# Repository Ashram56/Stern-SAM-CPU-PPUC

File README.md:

# Stern SAM CPU PPUC

A replacement CPU board for the Stern SAM pinball platform. A Raspberry Pi runs the original game ROM under PinMAME
through the [PPUC](https://github.com/PPUC) stack. An RP2354B on the same board drives the original IO power board bus (J1)
with its PIO, reads the switch matrix, dedicated switches and DIP switches, and can scan the original DMD.

- [docs/ARCHITECTURE.md](docs/ARCHITECTURE.md): architecture, bus timing, pin budget, safety, and open questions.
- [docs/reference/](docs/reference/): Stern SAM manual extracts (IO power driver and CPU/Sound board schematics, backbox,
  playfield, cabinet and coin door wiring).

Background:
- [Tron-Legacy-LE-ROM-Decryption/io/bus](https://github.com/Ashram56/Tron-Legacy-LE-ROM-Decryption/tree/main/io/bus):
  the CPU to IO board bus as the SAM ROM drives it.
- [Stern-SAM-Databus-Analysis](https://github.com/Ashram56/Stern-SAM-Databus-Analysis): J1 pinout and IO board schematic notes.

## Licence

- Firmware and software: GNU GPL v3 ([LICENSE](LICENSE)), matching PPUC.
- Hardware design files: CERN Open Hardware Licence v2, strongly reciprocal ([LICENSE-HARDWARE](LICENSE-HARDWARE)).
- The manual extracts in `docs/reference/` are Stern Pinball's material, kept for reference, and are not covered by
  either licence.

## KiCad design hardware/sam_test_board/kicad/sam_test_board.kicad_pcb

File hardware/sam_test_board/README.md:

# SAM universal test board (carte de test universelle, 48 voies)

One small board, made four times (JLCPCB batch of 5: one spare), that replaces the playfield and switch harnesses so
the new CPU board and the I/O Power Driver board 520-5249-00 can be tested with nothing at risk. Chosen by Vincent on
2026-11-18 instead of the single 250 x 150 mm board of `../driver_test_board/` (draft 0.1, abandoned).

## One channel (× 48)

Each pin of the four KK-396 12-pin headers A-D is a universal channel:

- **Load and indicator**: header common COMx → 33 k (0.5 W) → red LED → pin, green LED back in parallel. With COMx on a rail,
  a low-side output that turns on lights red (about 1.4 mA at 50 V, 0.5 mA at 20 V); with COMx on GND, an output
  that drives high lights green. A 3-pad solder jumper per header (JP1-JP4) puts COMx on RAILx (J5), on GND, or
  leaves it open (switch simulation, sense only).
- **Sense**: 100 k / 220 k (header A: 22 k 0.5 W / 47 k) into a 74HC165 input, whose clamp diode holds the node at 3.3 V
  up to 50 V (0.46 mA, header A 2.1 mA). 3 × 220 R load the 3.3 V rail (45 mA) so the clamp current cannot lift it.
  Header A also goes straight to GPIO8-19: fast enough for the 300 ns aux strobes and the CPU switch strobes.
- **Drive**: BSS123 (100 V, 170 mA) from pin to ground, gate from a 74HCT595 chain (100 k pull-down), to close a
  simulated switch.

## Roles

Same board and firmware, role set by the JP9/JP10 solder jumpers. Cables are straight: pin n of the SAM connector on
pin n of the header (a 9 or 10 way housing plugs on pins 1-9 / 1-10).

| role | JP9 / JP10 | A | B | C | D | commons |
|---|---|---|---|---|---|---|
| coils | open / open | IO J8 (1-8) | IO J9 (9-16) | IO J7 (17-24) | IO J6 (25-32) | A, B on +50 V, C, D on +20 V (J5) |
| lamps + aux | closed / open | IO J3 (aux strobes 9-12) | IO J12 (lamp strobes) | IO J13 (lamp columns) | IO J2 (aux data) | per the output type, see below |
| switch matrix | open / closed | CPU J1 (strobes) | CPU J6 (returns 1-8) | CPU J12 (returns 9-16) | CPU J2 (D-1..D-8) | open |
| dedicated | closed / closed | CPU J3 (D-9..D-16) | CPU J13 (D-17..D-24) | free | free | open |

Coil outputs have a 1N4004 flyback diode to their rail on the driver board: the rails must be on (J5 RAILx and the
driver board), otherwise every output reads ON through its diode. For the lamp board, an output that pulls low needs
its header common on the matching rail (red LED), one that drives high needs the common on GND (green LED); +18 V
also arrives on J13 pin 9, so channel C9 reads high (check the J13 9/10 swap on your IO board).

## Files

- `kicad/`: KiCad 9 schematic 0.2 (ERC 0, `kicad/erc.rpt`), PCB `sam_test_board.kicad_pcb` (DRC `kicad/drc.rpt`),
  project footprint library `sam_test_board.pretty` (PS1).
- `sam_test_board_schematic_v0.2.pdf`
- `fab/`: JLCPCB gerbers, BOM and CPL, renders (`tools/make_fab.sh`).
- `firmware/`: RP2354B firmware (Pico SDK 2.2), see its README. `pc/stb_probe.py`: PC tool for one or several boards.
- `tools/`: `place_stb.py` (placement from the netlist), `make_pro.py` (net classes), `finish_stb.py` (Freerouting
  session import, GND / GND_USB pours), `jlc_bom.py`, `jlc_rotcheck.py`, `make_fab.sh`. The schematic generator is
  `../driver_test_board/tools/design_stb.py` (`build_dtb.py design_stb <outdir>`, it shares kigen with the large board).
  From now on edit the KiCad files directly; the generators are the record of how the draft was made.

## PCB (0.2, reviewed 2026-11-18)

- 165 x 133 mm, 2 layers, 1.6 mm, every part on the top side (single-sided JLCPCB assembly). Four M3 holes in the
  corners (H1 = ground lug with pad).
- Headers A, B on the top edge, C, D on the bottom edge, J5 (rails + GND) top right, USB-C bottom right. KK-396
  friction ramps face inward.
- One column per channel facing its pin (red, green LED, 33 k, BSS123, 100 k gate, sense divider); the 74HC165 /
  74HCT595 in a strip across the middle under the channels they serve; RP2354B on the right.
- Net classes: HV (header pins, LED nodes, commons, rails): 0.6 mm clearance (IPC-2221 B2), 0.3 mm tracks.
  Default 0.2 / 0.15 mm (0.4 mm pitch QFN). Power 0.4 mm.
- Isolation: GND_USB (PC side) in the bottom-right corner (x > 129 mm, y > 111 mm), a strip with no copper separates
  it from GND; only U3 (ADuM3160) and PS1 (B0505S) straddle it.
- Fully routed: 0 open connection, ERC 0, DRC 0 error (`kicad/erc.rpt`, `kicad/drc.rpt`; the 2 warnings left are the
  USB-C silkscreen at the board edge). JP1-JP4 pads keep a 0.25 mm local clearance (solder jumper, 50 V max).
- Silkscreen: header names and pin numbers, J5 pin names, COM jumper sides (R = rail, G = GND), test point names, the
  role table (JP9 / JP10) and the LED legend.

## Review of 2026-11-18 (0.1 to 0.2)

Fixed:

1. **USB upstream series resistors.** The ADuM3160 needs a series resistor on each of its four data pins; UD+ / UD-
   went straight to the USB-C connector. Added R219 / R220 (24 R) between the connector (and its USBLC6) and U3.
2. **Power in the 50 V resistors.** Header A sense resistors (22 k) dissipate 96 mW at 50 V and 123 mW at 56 V on a
   125 mW 0805; the 33 k LED resistors 70 to 88 mW. Both are now 0.5 W 0805 parts (Panasonic ERJ-P06: C441987,
   C441956), same footprint: 25 % and 18 % of rating at 56 V.
3. **DC/DC module body.** PS1 used a bare 4-pin header footprint; the B0505S body (11.6 x 6.0 mm) reaches 4.8 mm
   left of the pin row and came within 0.3 mm of the C5 / C8 pads. PS1 now has its real outline and courtyard
   (`kicad/sam_test_board.pretty`), C5 / C8 are turned and moved (1.5 mm from the body).
4. **ADuM3160 decoupling.** C2 (VBUS1) and C3 / C4 (VDD1) were 5 to 9 mm from their pins; they now sit under pins
   1-2 and 3-5, each with its own via to the GND_USB return.
5. **4 open connections routed**: +1V1 to U5 pin 10 (via inside the QFN ring), COMB to JP2, VBUS_USB to U3 pin 1,
   G_B7 (needed G_B6 and S_B8 re-routed around it).
6. Symbols of test points, jumpers and holes marked "not in BOM" like their footprints (24 parity warnings gone).
7. Silkscreen labels added (there was no text on the board).

Checked and left as is:

- RP2354B pinout, core regulator, crystal, USB 27 R, QSPI_SS boot button, 74HC165 clamp current (0.46 mA, header A
  2.1 mA, 42 mA in total into +3V3 against 45 mA of fixed load), 74HCT595 at 5 V driving the BSS123 gates, rail
  dividers (2.7 V at 60 V), ADuM3160 strapping (full speed, pull-up always on), B0505S pin order.
- With the common on a rail and an output OFF, the sense divider still draws through the red LED: 0.14 mA on
  B-D (10 % of the ON current), **0.49 mA on header A (one third of ON)**. Header A LEDs glow when OFF; the PC
  reading is not affected. To avoid it use header A for the 20 V / logic connectors when a choice exists.
- NCP1117 with ceramic output capacitors only (10 u + 35 x 100 n): works in practice but is outside the datasheet
  ESR window. If +3V3 rings on the prototype, add a 10 u tantalum across C10 or use an LDO rated for ceramics in a
  later revision.
- BSS123 drives are only limited by the firmware role: closing a channel that is wired to a stiff source (lamp
  column +18 V) would exceed 170 mA.
- Spacing: SOT-23 / 0805 columns are 1.38 to 1.40 mm apart (3.96 mm pin pitch), the USB-C connector has parts at
  2.8 to 3.8 mm (C1, U2, R220, C4), PS1 body 1.5 mm from C5 / C8 / C2: below the 1.5 mm / 4 mm targets.
- Solder jumpers JP1-JP4 bridge 50 V with a 0.3 mm pad gap: never bridge the three pads (rail to GND short).

## JLCPCB

- 433 parts placed by JLC (432 SMD + PS1 B0505S through-hole), 35 LCSC codes, all in stock on the JLC assembly
  library on 2026-11-18 (lowest: 3.3 uH C167673 1 371, 22 k 0.5 W C441987 2 274, 74HCT595 C282339 6 348,
  ADuM3160 C284149 7 939, 33 k 0.5 W C441956 8 873).
- Hand soldered: the five KK-396 headers (Molex 26-60-4120 x 4, 26-60-4060), SWD and SYNC headers.
- CPL rotations checked against the EasyEDA footprint of each LCSC part (`tools/jlc_rotcheck.py`): offsets in
  `jlc_bom.py` (SOIC and SOT-23-6 +270, BSS123 and NCP1117 +180, B0505S +270 with its origin at the centre, USB-C
  origin shifted 1.575 mm). The tool prints CHECK for the LEDs, the NCP1117 and the buttons because their pad
  numbers differ; compared by pin name / position they are right (LED cathodes on the KiCad pad 1 side, NCP1117
  tab opposite the three pins).
- `fab/`: gerbers + drill (`sam_test_board-gerbers.zip`), BOM, CPL, renders. Regenerate with `tools/make_fab.sh`.

## Open

- Firmware untested on hardware. Check the placement preview on the JLCPCB order page before paying (LED and IC
  orientation), and re-check stock on the day of the order.

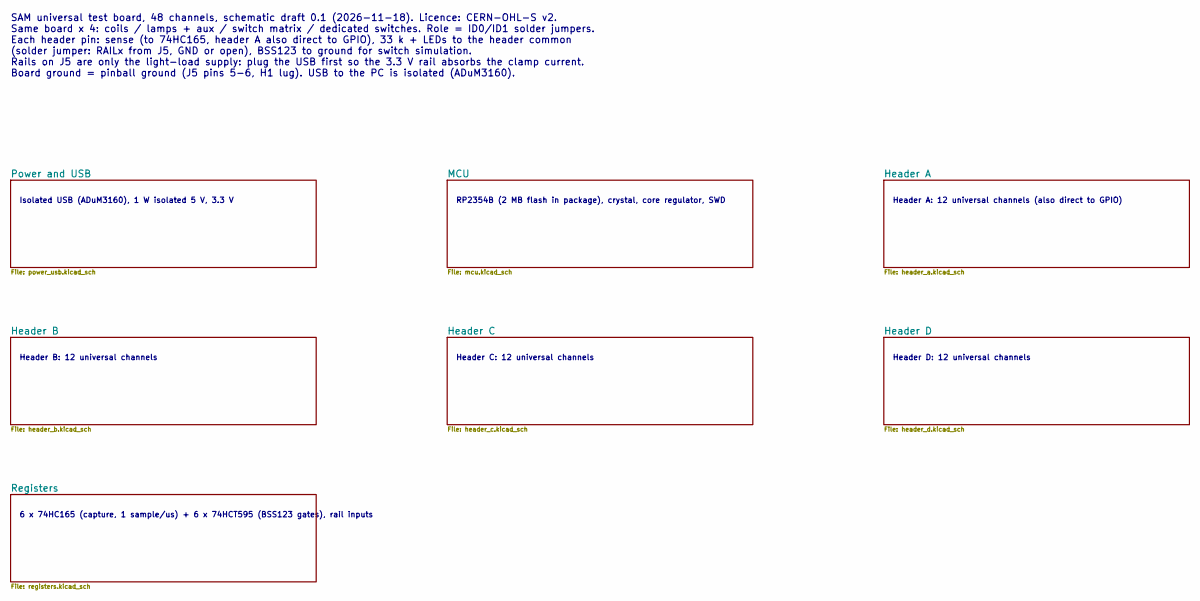
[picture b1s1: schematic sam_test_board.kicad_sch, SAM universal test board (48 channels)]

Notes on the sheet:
Isolated USB (ADuM3160), 1 W isolated 5 V, 3.3 V
RP2354B (2 MB flash in package), crystal, core regulator, SWD
Header A: 12 universal channels (also direct to GPIO)
Header B: 12 universal channels
Header C: 12 universal channels
Header D: 12 universal channels
6 x 74HC165 (capture, 1 sample/us) + 6 x 74HCT595 (BSS123 gates), rail inputs
SAM universal test board, 48 channels, schematic draft 0.1 (2026-11-18). Licence: CERN-OHL-S v2. Same board x 4: coils / lamps + aux / switch matrix / dedicated switches. Role = ID0/ID1 solder jumpers. Each header pin: sense (to 74HC165, header A also direct to GPIO), 33 k + LEDs to the header comm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

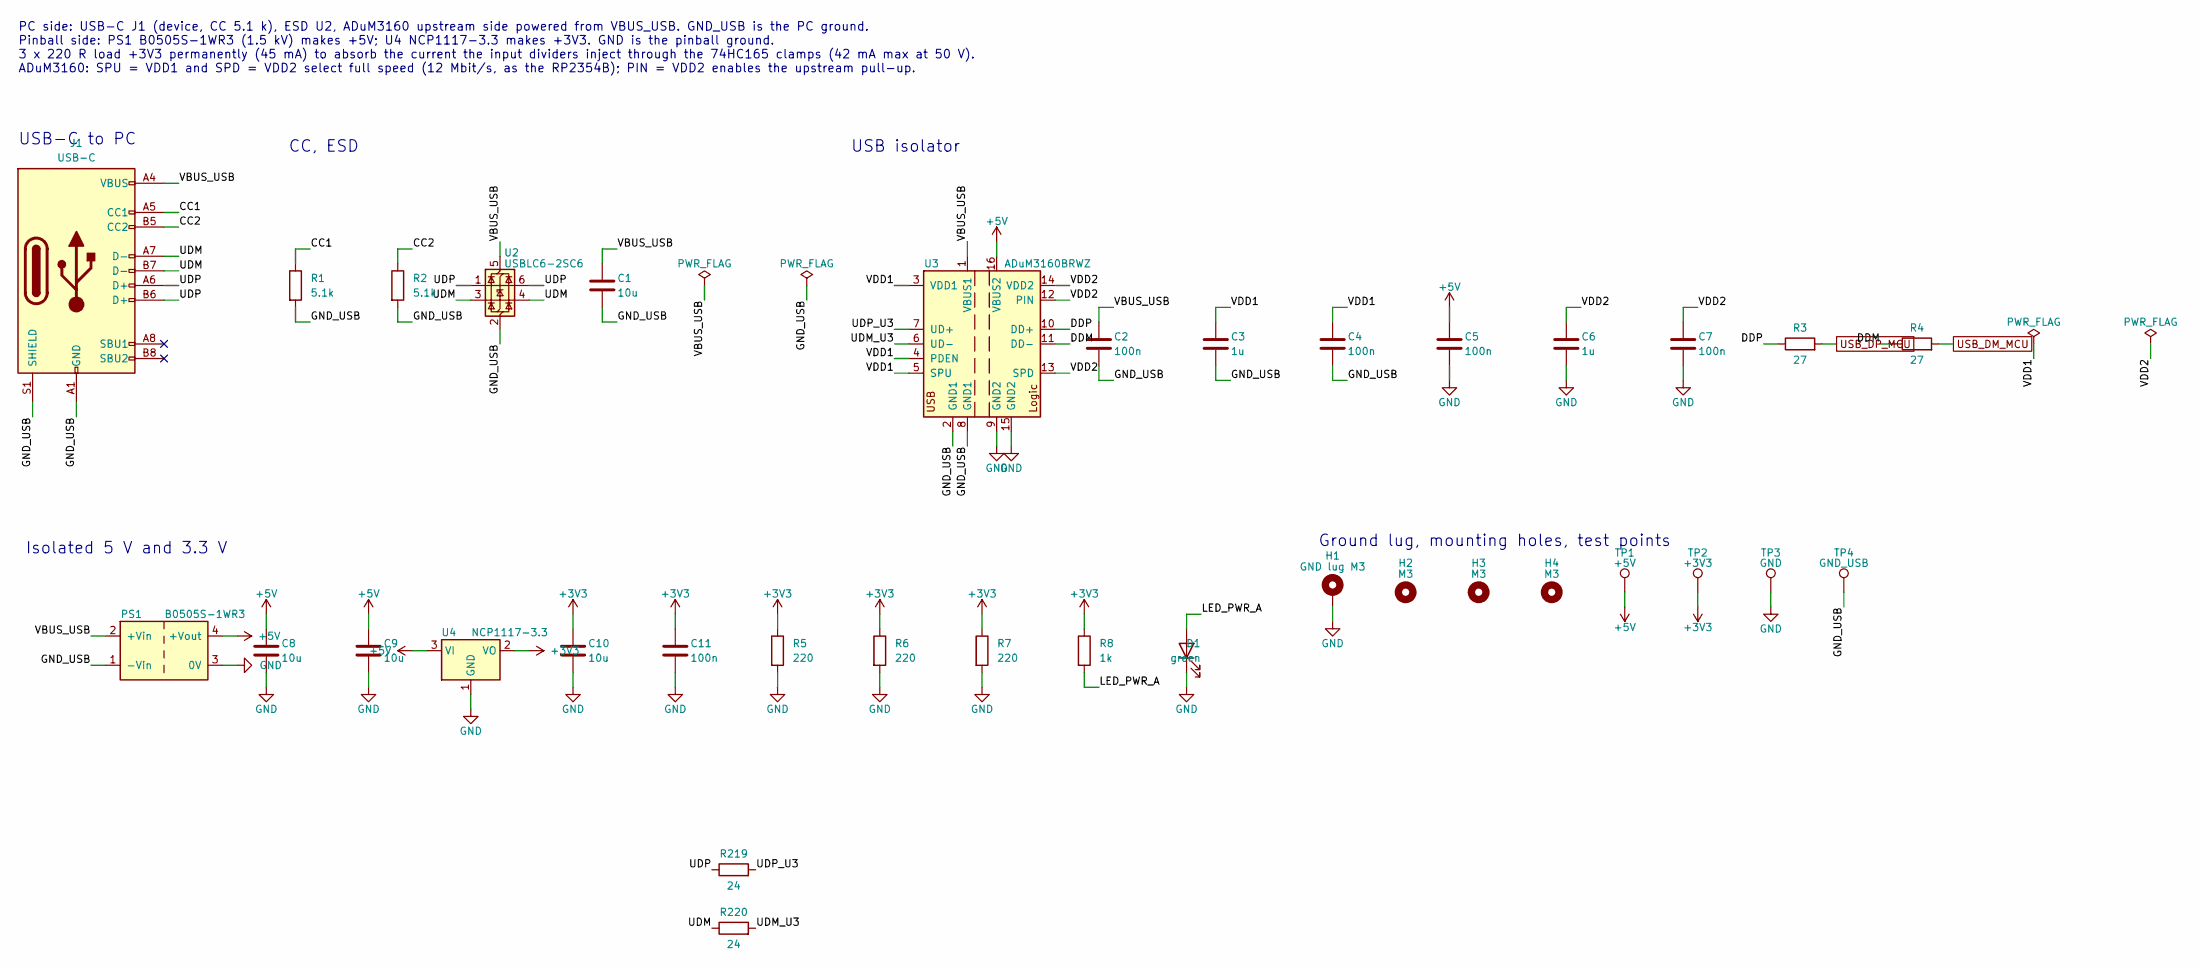
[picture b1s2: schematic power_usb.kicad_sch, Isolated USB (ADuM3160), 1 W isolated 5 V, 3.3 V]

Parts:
C1, C8, C9, C10: 10u; C_0805_2012Metric
C2, C4, C5, C7, C11: 100n; C_0805_2012Metric
C3, C6: 1u; C_0805_2012Metric
D1: green; LED_0805_2012Metric
H1: GND lug M3; MountingHole_3.2mm_M3_Pad_Via
H2, H3, H4: M3; MountingHole_3.2mm_M3
J1: USB-C; USB_C_Receptacle_HRO_TYPE-C-31-M-12
PS1: B0505S-1WR3; PinHeader_1x04_P2.54mm_Vertical
R1, R2: 5.1k; R_0805_2012Metric
R3, R4: 27; R_0805_2012Metric
R5, R6, R7: 220; R_0805_2012Metric
R8: 1k; R_0805_2012Metric
R219, R220: 24; R_0805_2012Metric
TP1: +5V; TestPoint_Pad_D1.5mm
TP2: +3V3; TestPoint_Pad_D1.5mm
TP3: GND; TestPoint_Pad_D1.5mm
TP4: GND_USB; TestPoint_Pad_D1.5mm
U2: USBLC6-2SC6; SOT-23-6
U3: ADuM3160BRWZ; SOIC-16W_7.5x10.3mm_P1.27mm
U4: NCP1117-3.3; SOT-223-3_TabPin2

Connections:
+3V3: C10.1, C11.1, R5.1, R6.1, R7.1, R8.1, TP2.1, U4.2 (VO); also elsewhere on the board
+5V: C5.1, C8.1, C9.1, PS1.4 (+Vout), TP1.1, U3.16 (VBUS2), U4.3 (VI); also elsewhere on the board
/Power and USB/CC1: J1.A5 (CC1), R1.1
/Power and USB/CC2: J1.B5 (CC2), R2.1
/Power and USB/DDM: R4.1, U3.11 (DD-)
/Power and USB/DDP: R3.1, U3.10 (DD+)
/Power and USB/GND_USB: C1.2, C2.2, C3.2, C4.2, J1.A1 (GND), J1.A12 (GND), J1.B1 (GND), J1.B12 (GND), J1.S1 (SHIELD), PS1.1 (-Vin), R1.2, R2.2, TP4.1, U2.2 (GND), U3.2 (GND1), U3.8 (GND1)
/Power and USB/LED_PWR_A: D1.2 (A), R8.2
/Power and USB/UDM: J1.A7 (D-), J1.B7 (D-), R220.1, U2.3 (I/O2), U2.4 (I/O2)
/Power and USB/UDM_U3: R220.2, U3.6 (UD-)
/Power and USB/UDP: J1.A6 (D+), J1.B6 (D+), R219.1, U2.1 (I/O1), U2.6 (I/O1)
/Power and USB/UDP_U3: R219.2, U3.7 (UD+)
/Power and USB/VBUS_USB: C1.1, C2.1, J1.A4 (VBUS), J1.A9 (VBUS), J1.B4 (VBUS), J1.B9 (VBUS), PS1.2 (+Vin), U2.5 (VBUS), U3.1 (VBUS1)
/Power and USB/VDD1: C3.1, C4.1, U3.3 (VDD1), U3.4 (PDEN), U3.5 (SPU)
/Power and USB/VDD2: C6.1, C7.1, U3.12 (PIN), U3.13 (SPD), U3.14 (VDD2)
GND: C5.2, C6.2, C7.2, C8.2, C9.2, C10.2, C11.2, D1.1 (K), H1.1, PS1.3 (0V), R5.2, R6.2, R7.2, TP3.1, U3.9 (GND2), U3.15 (GND2), U4.1 (GND); also elsewhere on the board
USB_DM_MCU: R4.2; also elsewhere on the board
USB_DP_MCU: R3.2; also elsewhere on the board

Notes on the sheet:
PC side: USB-C J1 (device, CC 5.1 k), ESD U2, ADuM3160 upstream side powered from VBUS_USB. GND_USB is the PC ground. Pinball side: PS1 B0505S-1WR3 (1.5 kV) makes +5V; U4 NCP1117-3.3 makes +3V3. GND is the pinball ground. 3 x 220 R load +3V3 permanently (45 mA) to absorb the current the input divid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
USB-C to PC
CC, ESD
USB isolator
Isolated 5 V and 3.3 V
Ground lug, mounting holes, test points

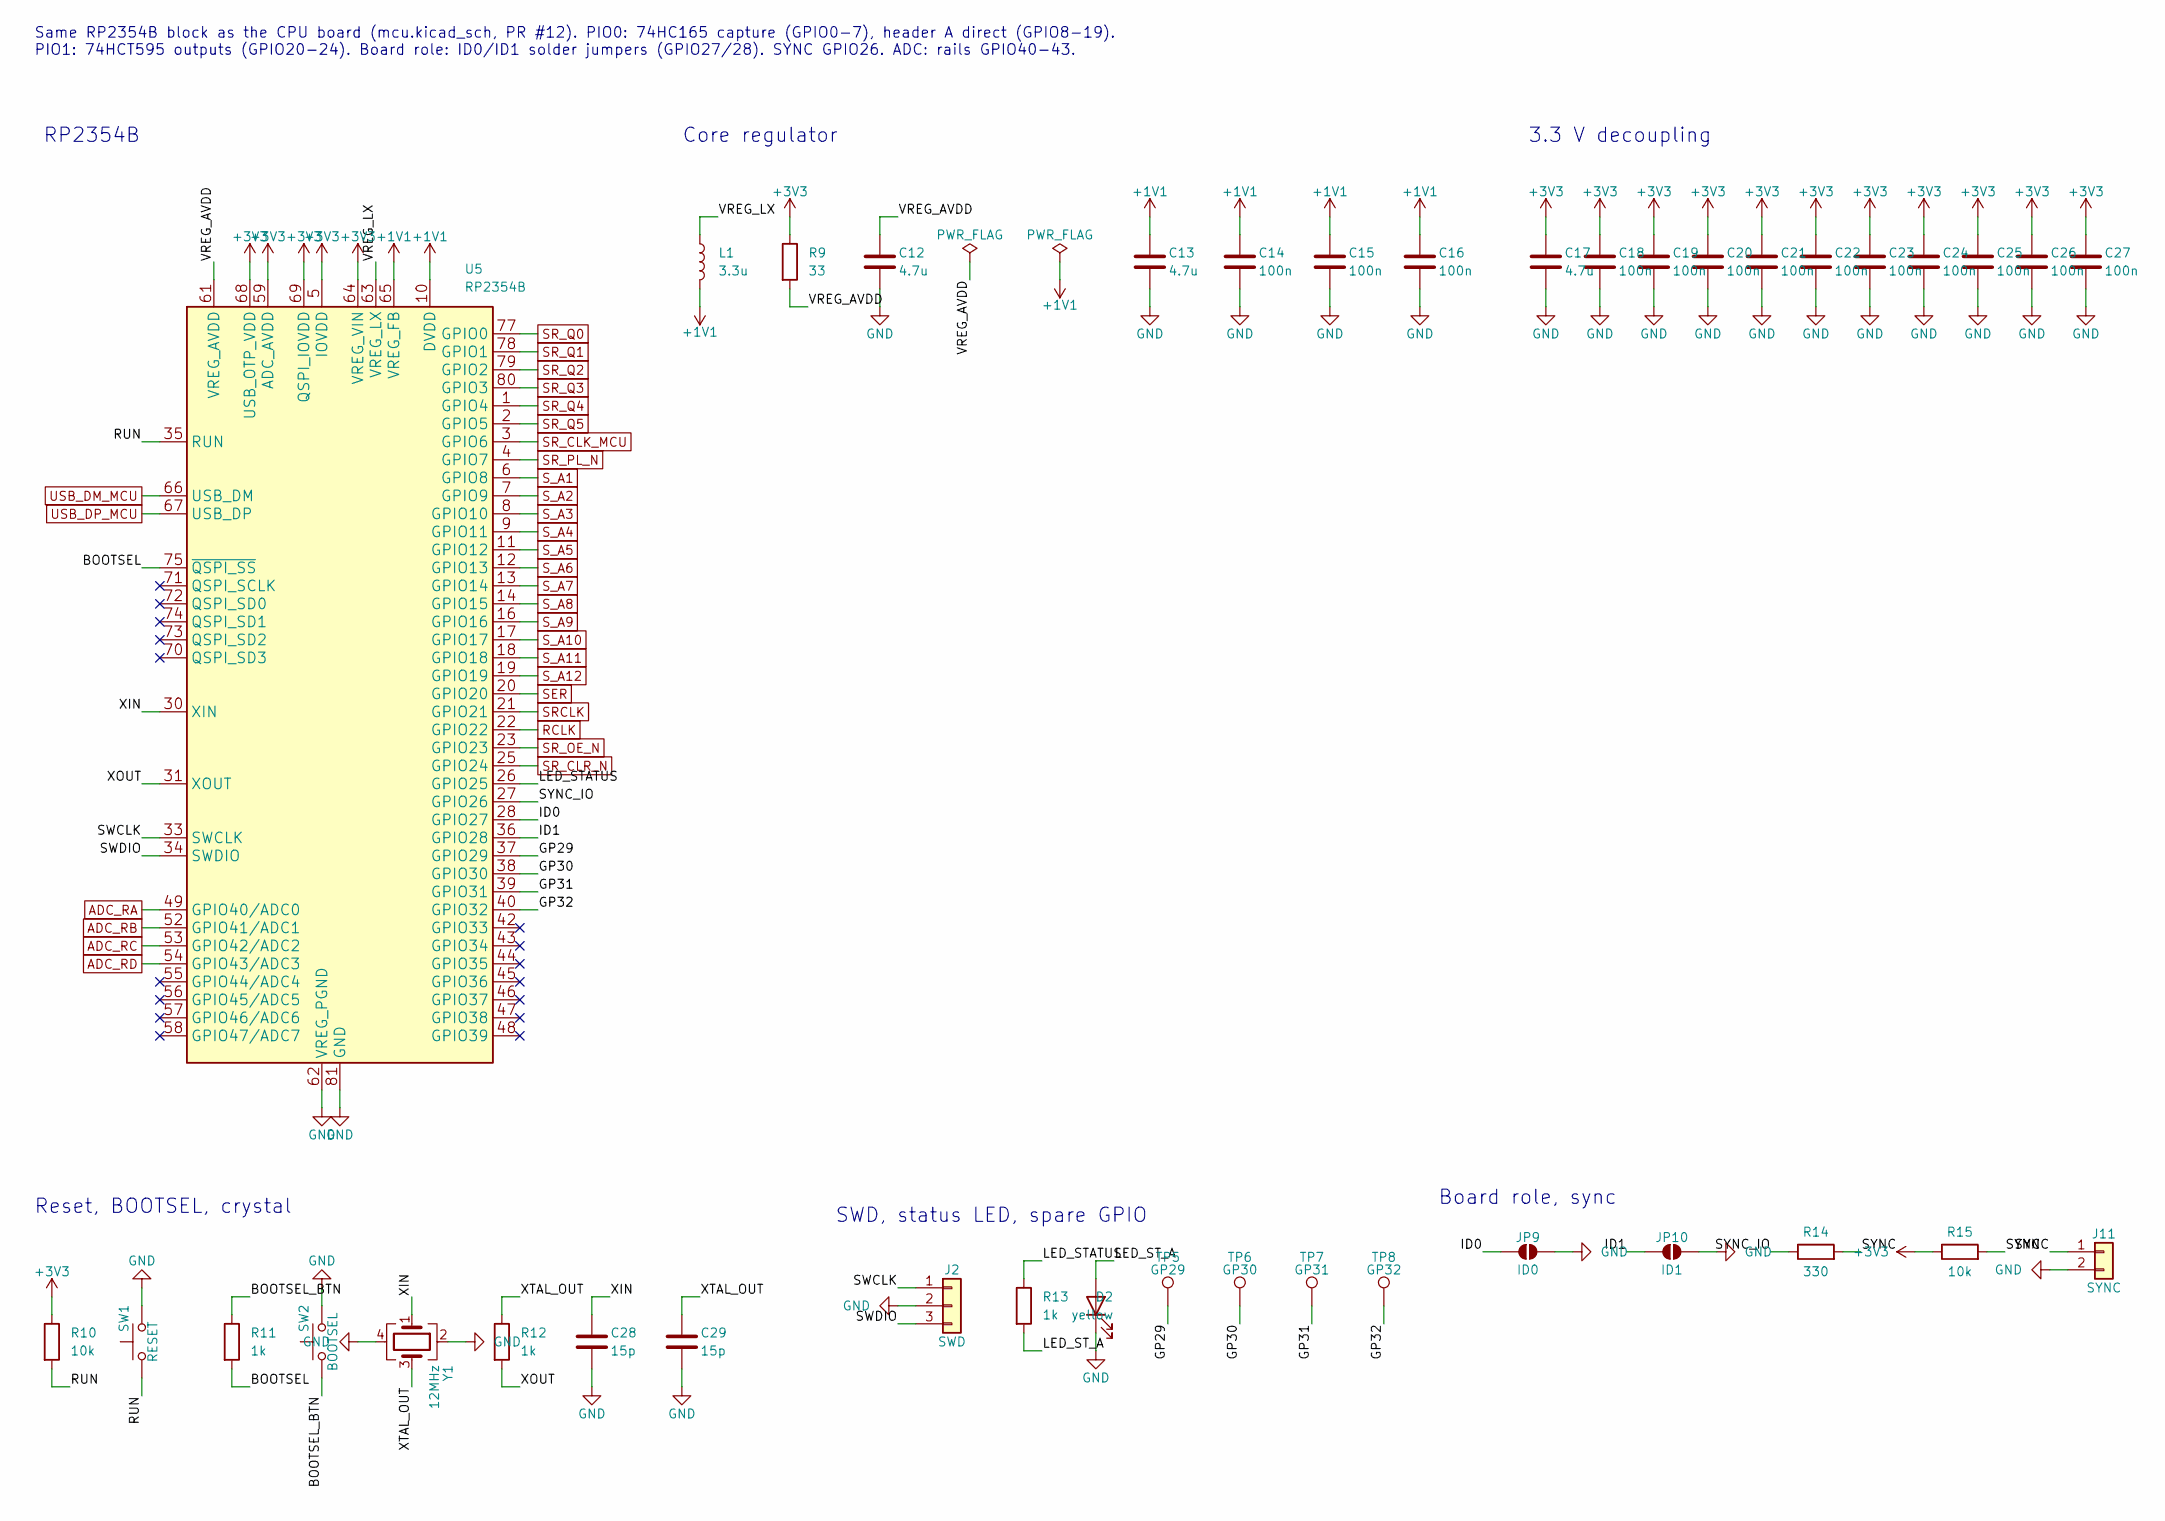
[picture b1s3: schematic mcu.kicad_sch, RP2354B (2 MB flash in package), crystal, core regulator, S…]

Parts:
C12, C13, C17: 4.7u; C_0805_2012Metric
C14, C15, C16, C18, C19, C20, C21, C22, C23, C24, C25, C26, C27: 100n; C_0805_2012Metric
C28, C29: 15p; C_0805_2012Metric
D2: yellow; LED_0805_2012Metric
J2: SWD; PinHeader_1x03_P2.54mm_Vertical
J11: SYNC; PinHeader_1x02_P2.54mm_Vertical
JP9: ID0; SolderJumper-2_P1.3mm_Open_Pad1.0x1.5mm
JP10: ID1; SolderJumper-2_P1.3mm_Open_Pad1.0x1.5mm
L1: 3.3u; L_Cenker_CKCS201610
R9: 33; R_0805_2012Metric
R10, R15: 10k; R_0805_2012Metric
R11, R12, R13: 1k; R_0805_2012Metric
R14: 330; R_0805_2012Metric
SW1: RESET; SW_SPST_TL3342
SW2: BOOTSEL; SW_SPST_TL3342
TP5: GP29; TestPoint_Pad_D1.5mm
TP6: GP30; TestPoint_Pad_D1.5mm
TP7: GP31; TestPoint_Pad_D1.5mm
TP8: GP32; TestPoint_Pad_D1.5mm
U5: RP2354B; QFN-80-1EP_10x10mm_P0.4mm_EP3.4x3.4mm
Y1: 12MHz; Crystal_SMD_3225-4Pin_3.2x2.5mm

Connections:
+1V1: C13.1, C14.1, C15.1, C16.1, L1.2, U5.10 (DVDD), U5.32 (DVDD), U5.51 (DVDD), U5.65 (VREG_FB)
+3V3: C17.1, C18.1, C19.1, C20.1, C21.1, C22.1, C23.1, C24.1, C25.1, C26.1, C27.1, R9.1, R10.1, R15.1, U5.5 (IOVDD), U5.15 (IOVDD), U5.24 (IOVDD), U5.29 (IOVDD), U5.41 (IOVDD), U5.50 (IOVDD), U5.59 (ADC_AVDD), U5.60 (IOVDD), U5.64 (VREG_VIN), U5.68 (USB_OTP_VDD), U5.69 (QSPI_IOVDD), U5.76 (IOVDD); also elsewhere on the board
/MCU/BOOTSEL: R11.2, U5.75 (~QSPI_SS)
/MCU/BOOTSEL_BTN: R11.1, SW2.1
/MCU/GP29: TP5.1, U5.37 (GPIO29)
/MCU/GP30: TP6.1, U5.38 (GPIO30)
/MCU/GP31: TP7.1, U5.39 (GPIO31)
/MCU/GP32: TP8.1, U5.40 (GPIO32)
/MCU/ID0: JP9.1 (A), U5.28 (GPIO27)
/MCU/ID1: JP10.1 (A), U5.36 (GPIO28)
/MCU/LED_STATUS: R13.1, U5.26 (GPIO25)
/MCU/LED_ST_A: D2.2 (A), R13.2
/MCU/RUN: R10.2, SW1.1, U5.35 (RUN)
/MCU/SWCLK: J2.1, U5.33 (SWCLK)
/MCU/SWDIO: J2.3, U5.34 (SWDIO)
/MCU/SYNC: J11.1, R14.2, R15.2
/MCU/SYNC_IO: R14.1, U5.27 (GPIO26)
/MCU/VREG_AVDD: C12.1, R9.2, U5.61 (VREG_AVDD)
/MCU/VREG_LX: L1.1, U5.63 (VREG_LX)
/MCU/XIN: C28.1, U5.30 (XIN), Y1.1
/MCU/XOUT: R12.2, U5.31 (XOUT)
/MCU/XTAL_OUT: C29.1, R12.1, Y1.3
ADC_RA: U5.49 (GPIO40/ADC0); also elsewhere on the board
ADC_RB: U5.52 (GPIO41/ADC1); also elsewhere on the board
ADC_RC: U5.53 (GPIO42/ADC2); also elsewhere on the board
ADC_RD: U5.54 (GPIO43/ADC3); also elsewhere on the board
GND: C12.2, C13.2, C14.2, C15.2, C16.2, C17.2, C18.2, C19.2, C20.2, C21.2, C22.2, C23.2, C24.2, C25.2, C26.2, C27.2, C28.2, C29.2, D2.1 (K), J2.2, J11.2, JP9.2 (B), JP10.2 (B), SW1.2, SW2.2, U5.62 (VREG_PGND), U5.81 (GND), Y1.2, Y1.4; also elsewhere on the board
RCLK: U5.22 (GPIO22); also elsewhere on the board
SER: U5.20 (GPIO20); also elsewhere on the board
SRCLK: U5.21 (GPIO21); also elsewhere on the board
SR_CLK_MCU: U5.3 (GPIO6); also elsewhere on the board
SR_CLR_N: U5.25 (GPIO24); also elsewhere on the board
SR_OE_N: U5.23 (GPIO23); also elsewhere on the board
SR_PL_N: U5.4 (GPIO7); also elsewhere on the board
SR_Q0: U5.77 (GPIO0); also elsewhere on the board
SR_Q1: U5.78 (GPIO1); also elsewhere on the board
SR_Q2: U5.79 (GPIO2); also elsewhere on the board
SR_Q3: U5.80 (GPIO3); also elsewhere on the board
SR_Q4: U5.1 (GPIO4); also elsewhere on the board
SR_Q5: U5.2 (GPIO5); also elsewhere on the board
S_A1: U5.6 (GPIO8); also elsewhere on the board
S_A2: U5.7 (GPIO9); also elsewhere on the board
S_A3: U5.8 (GPIO10); also elsewhere on the board
S_A4: U5.9 (GPIO11); also elsewhere on the board
S_A5: U5.11 (GPIO12); also elsewhere on the board
S_A6: U5.12 (GPIO13); also elsewhere on the board
S_A7: U5.13 (GPIO14); also elsewhere on the board
S_A8: U5.14 (GPIO15); also elsewhere on the board
S_A9: U5.16 (GPIO16); also elsewhere on the board
S_A10: U5.17 (GPIO17); also elsewhere on the board
S_A11: U5.18 (GPIO18); also elsewhere on the board
S_A12: U5.19 (GPIO19); also elsewhere on the board
USB_DM_MCU: U5.66 (USB_DM); also elsewhere on the board
USB_DP_MCU: U5.67 (USB_DP); also elsewhere on the board

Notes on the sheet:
Same RP2354B block as the CPU board (mcu.kicad_sch, PR #12). PIO0: 74HC165 capture (GPIO0-7), header A direct (GPIO8-19). PIO1: 74HCT595 outputs (GPIO20-24). Board role: ID0/ID1 solder jumpers (GPIO27/28). SYNC GPIO26. ADC: rails GPIO40-43.
RP2354B
Core regulator
3.3 V decoupling
Reset, BOOTSEL, crystal
SWD, status LED, spare GPIO
Board role, sync

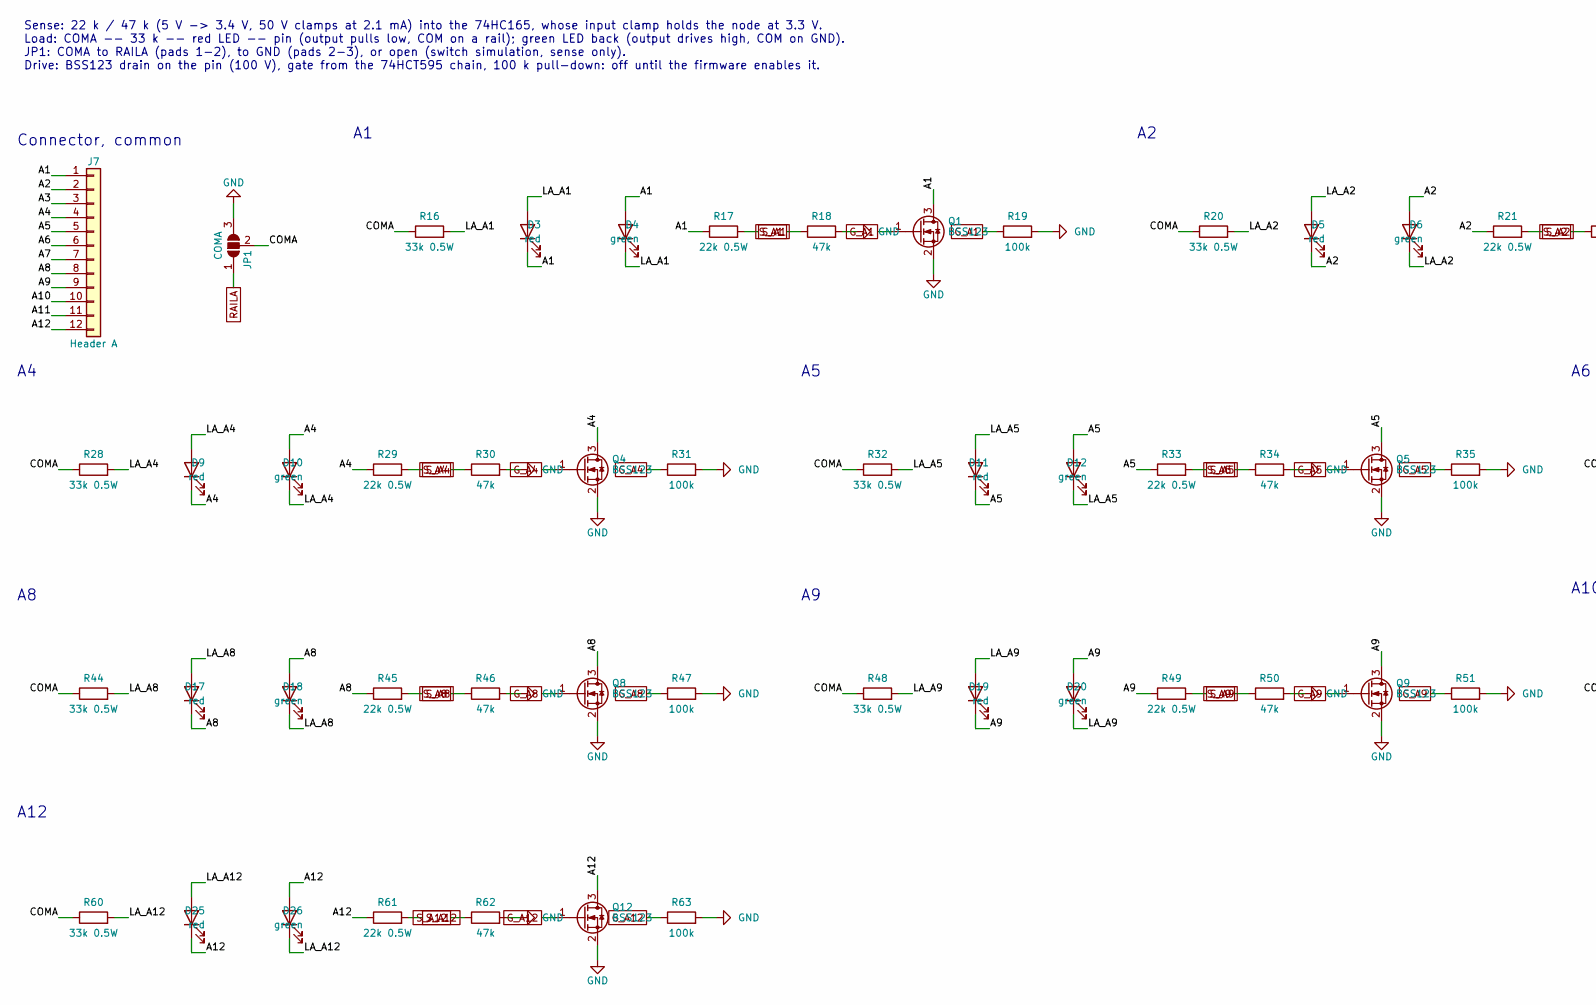
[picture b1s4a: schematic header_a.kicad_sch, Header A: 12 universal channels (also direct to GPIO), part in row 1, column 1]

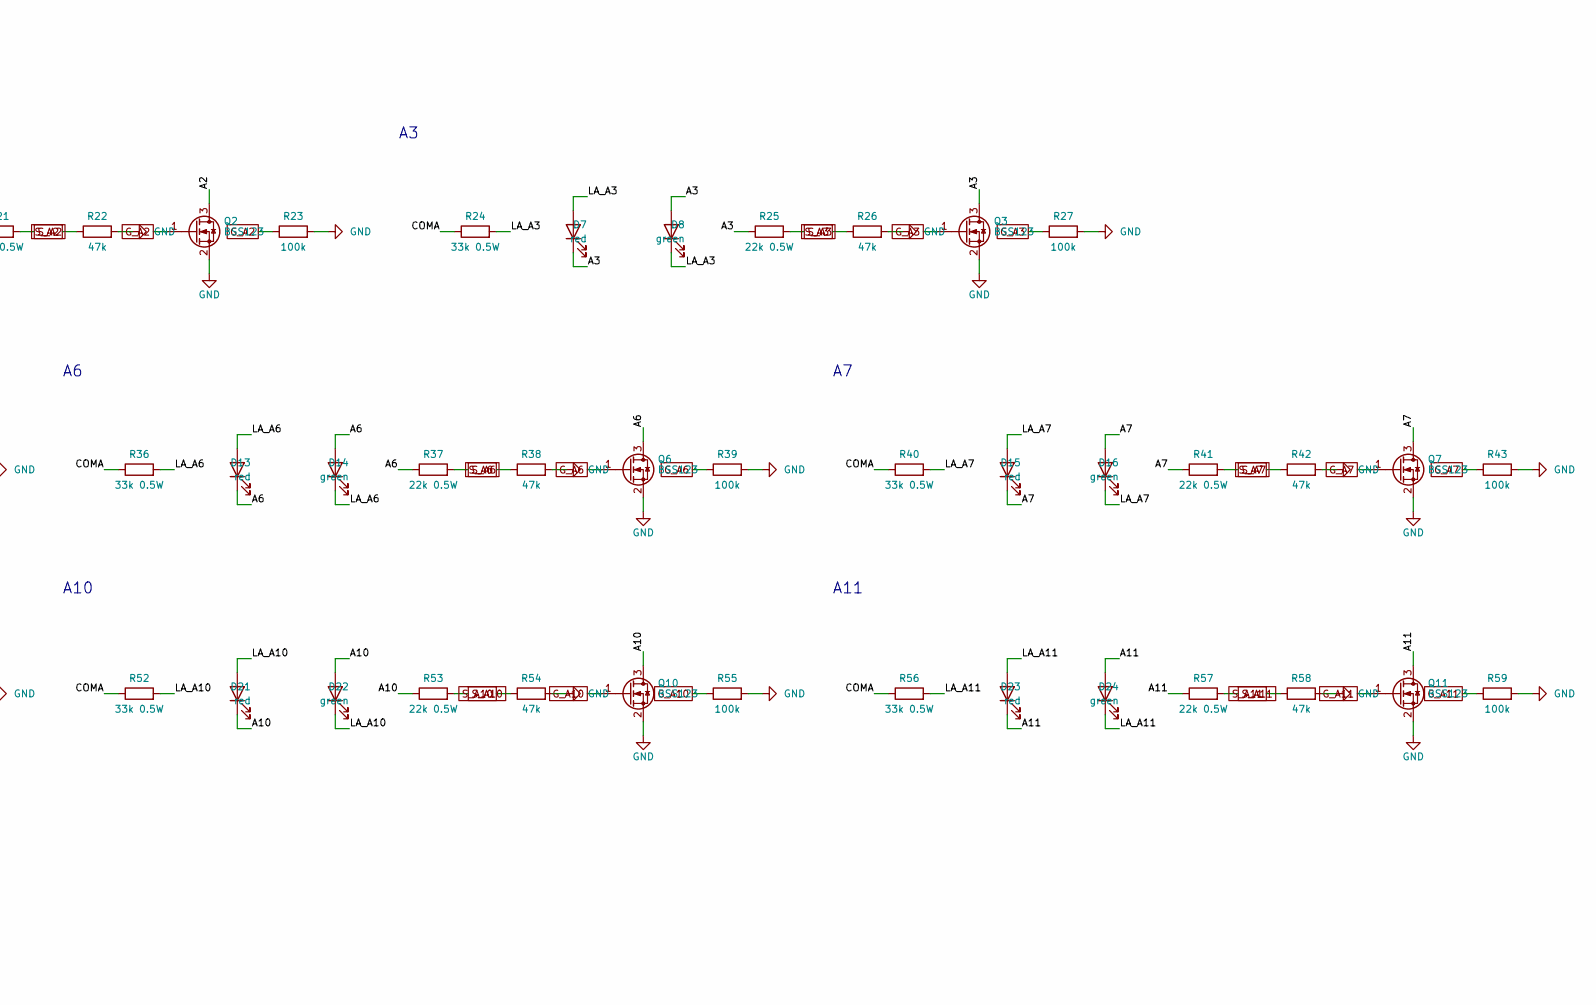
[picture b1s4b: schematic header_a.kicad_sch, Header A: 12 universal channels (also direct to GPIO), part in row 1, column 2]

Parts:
D3, D5, D7, D9, D11, D13, D15, D17, D19, D21, D23, D25: red; LED_0805_2012Metric
D4, D6, D8, D10, D12, D14, D16, D18, D20, D22, D24, D26: green; LED_0805_2012Metric
J7: Header A; Molex_KK-396_A-41791-0012_1x12_P3.96mm_Vertical
JP1: COMA; SolderJumper-3_P1.3mm_Open_Pad1.0x1.5mm
Q1, Q2, Q3, Q4, Q5, Q6, Q7, Q8, Q9, Q10, Q11, Q12: BSS123; SOT-23
R16, R20, R24, R28, R32, R36, R40, R44, R48, R52, R56, R60: 33k 0.5W; R_0805_2012Metric
R17, R21, R25, R29, R33, R37, R41, R45, R49, R53, R57, R61: 22k 0.5W; R_0805_2012Metric
R18, R22, R26, R30, R34, R38, R42, R46, R50, R54, R58, R62: 47k; R_0805_2012Metric
R19, R23, R27, R31, R35, R39, R43, R47, R51, R55, R59, R63: 100k; R_0805_2012Metric

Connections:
/Header A/A1: D3.1 (K), D4.2 (A), J7.1, Q1.3 (D), R17.1
/Header A/A2: D5.1 (K), D6.2 (A), J7.2, Q2.3 (D), R21.1
/Header A/A3: D7.1 (K), D8.2 (A), J7.3, Q3.3 (D), R25.1
/Header A/A4: D9.1 (K), D10.2 (A), J7.4, Q4.3 (D), R29.1
/Header A/A5: D11.1 (K), D12.2 (A), J7.5, Q5.3 (D), R33.1
/Header A/A6: D13.1 (K), D14.2 (A), J7.6, Q6.3 (D), R37.1
/Header A/A7: D15.1 (K), D16.2 (A), J7.7, Q7.3 (D), R41.1
/Header A/A8: D17.1 (K), D18.2 (A), J7.8, Q8.3 (D), R45.1
/Header A/A9: D19.1 (K), D20.2 (A), J7.9, Q9.3 (D), R49.1
/Header A/A10: D21.1 (K), D22.2 (A), J7.10, Q10.3 (D), R53.1
/Header A/A11: D23.1 (K), D24.2 (A), J7.11, Q11.3 (D), R57.1
/Header A/A12: D25.1 (K), D26.2 (A), J7.12, Q12.3 (D), R61.1
/Header A/COMA: JP1.2 (C), R16.1, R20.1, R24.1, R28.1, R32.1, R36.1, R40.1, R44.1, R48.1, R52.1, R56.1, R60.1
/Header A/LA_A1: D3.2 (A), D4.1 (K), R16.2
/Header A/LA_A2: D5.2 (A), D6.1 (K), R20.2
/Header A/LA_A3: D7.2 (A), D8.1 (K), R24.2
/Header A/LA_A4: D9.2 (A), D10.1 (K), R28.2
/Header A/LA_A5: D11.2 (A), D12.1 (K), R32.2
/Header A/LA_A6: D13.2 (A), D14.1 (K), R36.2
/Header A/LA_A7: D15.2 (A), D16.1 (K), R40.2
/Header A/LA_A8: D17.2 (A), D18.1 (K), R44.2
/Header A/LA_A9: D19.2 (A), D20.1 (K), R48.2
/Header A/LA_A10: D21.2 (A), D22.1 (K), R52.2
/Header A/LA_A11: D23.2 (A), D24.1 (K), R56.2
/Header A/LA_A12: D25.2 (A), D26.1 (K), R60.2
GND: JP1.3 (B), Q1.2 (S), Q2.2 (S), Q3.2 (S), Q4.2 (S), Q5.2 (S), Q6.2 (S), Q7.2 (S), Q8.2 (S), Q9.2 (S), Q10.2 (S), Q11.2 (S), Q12.2 (S), R18.2, R19.2, R22.2, R23.2, R26.2, R27.2, R30.2, R31.2, R34.2, R35.2, R38.2, R39.2, R42.2, R43.2, R46.2, R47.2, R50.2, R51.2, R54.2, R55.2, R58.2, R59.2, R62.2, R63.2; also elsewhere on the board
G_A1: Q1.1 (G), R19.1; also elsewhere on the board
G_A2: Q2.1 (G), R23.1; also elsewhere on the board
G_A3: Q3.1 (G), R27.1; also elsewhere on the board
G_A4: Q4.1 (G), R31.1; also elsewhere on the board
G_A5: Q5.1 (G), R35.1; also elsewhere on the board
G_A6: Q6.1 (G), R39.1; also elsewhere on the board
G_A7: Q7.1 (G), R43.1; also elsewhere on the board
G_A8: Q8.1 (G), R47.1; also elsewhere on the board
G_A9: Q9.1 (G), R51.1; also elsewhere on the board
G_A10: Q10.1 (G), R55.1; also elsewhere on the board
G_A11: Q11.1 (G), R59.1; also elsewhere on the board
G_A12: Q12.1 (G), R63.1; also elsewhere on the board
RAILA: JP1.1 (A); also elsewhere on the board
S_A1: R17.2, R18.1; also elsewhere on the board
S_A2: R21.2, R22.1; also elsewhere on the board
S_A3: R25.2, R26.1; also elsewhere on the board
S_A4: R29.2, R30.1; also elsewhere on the board
S_A5: R33.2, R34.1; also elsewhere on the board
S_A6: R37.2, R38.1; also elsewhere on the board
S_A7: R41.2, R42.1; also elsewhere on the board
S_A8: R45.2, R46.1; also elsewhere on the board
S_A9: R49.2, R50.1; also elsewhere on the board
S_A10: R53.2, R54.1; also elsewhere on the board
S_A11: R57.2, R58.1; also elsewhere on the board
S_A12: R61.2, R62.1; also elsewhere on the board

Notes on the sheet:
Sense: 22 k / 47 k (5 V -> 3.4 V, 50 V clamps at 2.1 mA) into the 74HC165, whose input clamp holds the node at 3.3 V. Load: COMA -- 33 k -- red LED -- pin (output pulls low, COM on a rail); green LED back (output drives high, COM on GND). JP1: COMA to RAILA (pads 1-2), to GND (pads 2-3), or open (s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
Connector, common
A10
A11
A12

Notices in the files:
hardware/driver_test_board/kicad/aux.kicad_sch:
Stern SAM CPU PPUC (CERN-OHL-S v2)
